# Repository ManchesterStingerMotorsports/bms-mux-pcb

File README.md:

# BMS MUX PCB

Initially the pcb scope was only for multiplexing 16 temperature sensor signals to 8, but the scope grew bigger and other stuffs were added.

Designed in Kicad V8

## V1 3D Render

### [Schematic](<docs/Schematic V1.pdf>)

### [Layout](<docs/PCB Layout V1.pdf>)

### [Copper Layers](<docs/PCB Copper Layers V1.pdf>)

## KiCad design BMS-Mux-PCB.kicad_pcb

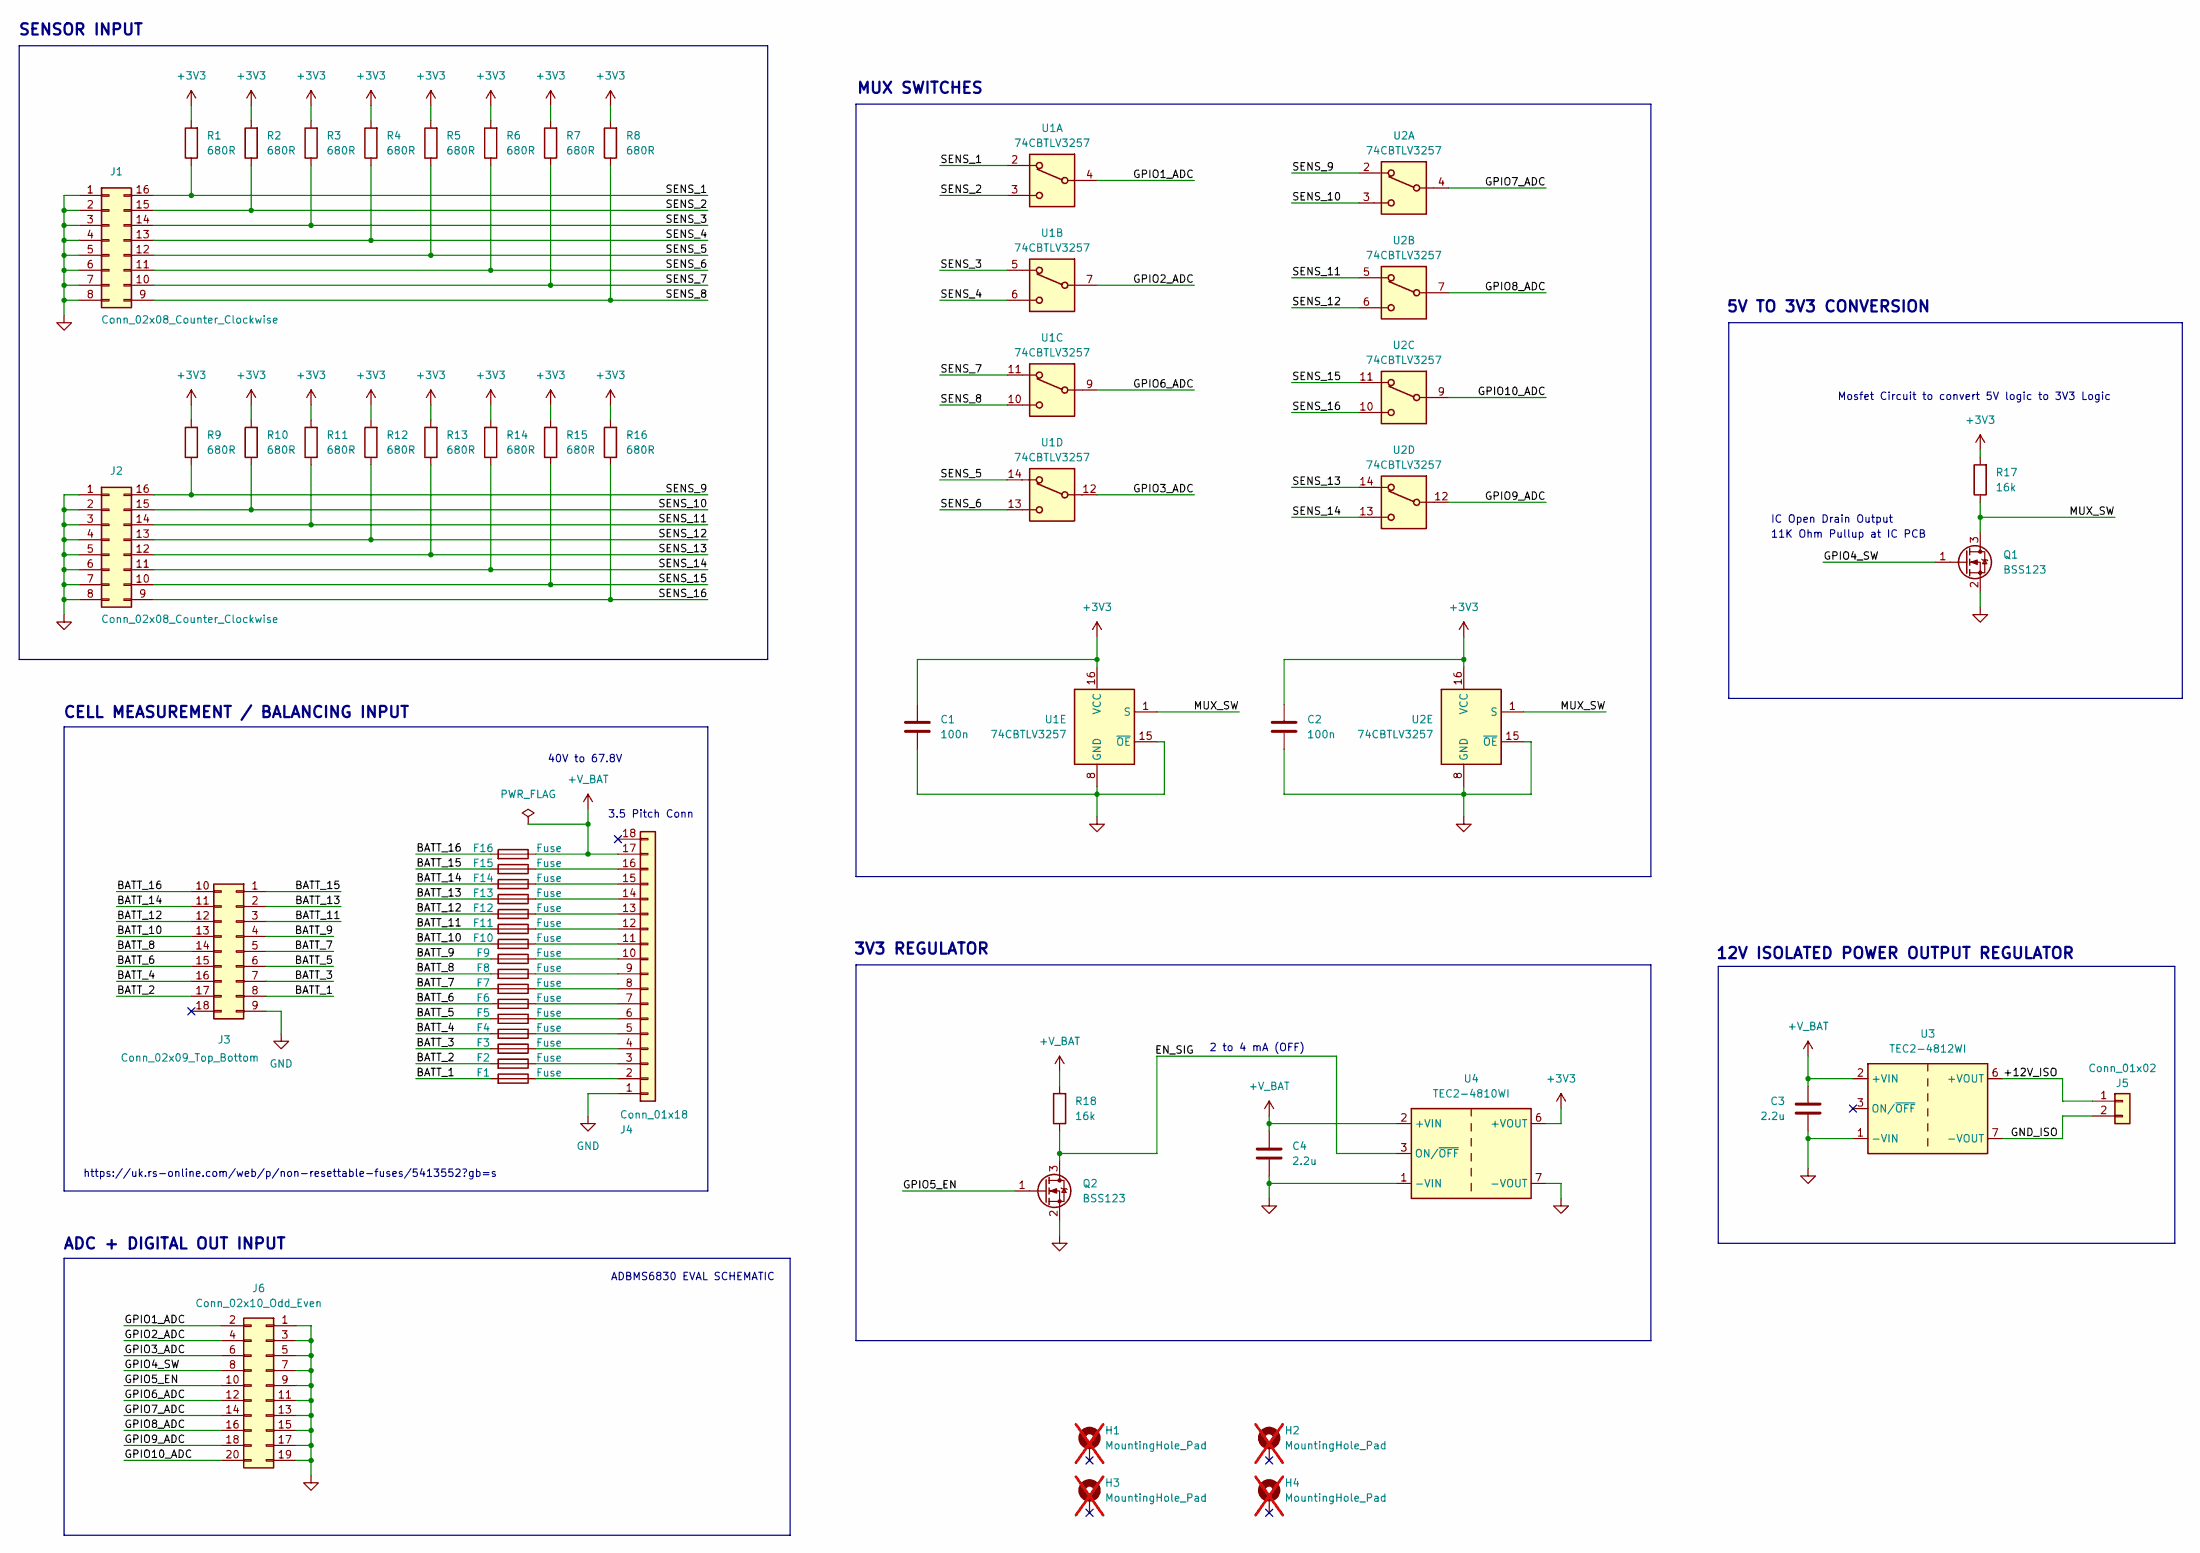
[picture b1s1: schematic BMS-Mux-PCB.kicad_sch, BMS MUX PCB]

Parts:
C1, C2: 100n; C_0603_1608Metric_Pad1.08x0.95mm_HandSolder; Manufacturer Part Number CL10B104KB85PND
C3, C4: 2.2u; C_1206_3216Metric_Pad1.33x1.80mm_HandSolder; Manufacturer Part Number 885382208016
F1, F2, F3, F4, F5, F6, F7, F8, F9, F10, F11, F12, F13, F14, F15, F16: Fuse; Fuse_1206_3216Metric_Pad1.42x1.75mm_HandSolder; Manufacturer Part Number 0466.250NR
H1, H2, H3, H4: MountingHole_Pad; Mounting_Hole; not fitted
J1, J2: Conn_02x08_Counter_Clockwise; Molex_Micro-Fit_3.0_43045-1600_2x08_P3.00mm_Horizontal; Manufacturer Part Number 43045-1600
J3: Conn_02x09_Top_Bottom; Molex_Micro-Fit_3.0_43045-1800_2x09_P3.00mm_Horizontal; Manufacturer Part Number 43045-1800
J4: Conn_01x18; Wago_734-148_1x18_P3.50mm_Vertical; Manufacturer Part Number 1945151 (x2)
J5: Conn_01x02; Molex_Micro-Fit_3.0_43650-0200_1x02_P3.00mm_Horizontal; Manufacturer Part Number 43650-0200
J6: Conn_02x10_Odd_Even; PinHeader_2x10_P2.54mm_Vertical; Manufacturer Part Number PH2-20-UA
Q1, Q2: BSS123; SOT-23; Manufacturer Part Number BSS123L
R1, R2, R3, R4, R5, R6, R7, R8, R9, R10, R11, R12, R13, R14, R15, R16: 680R; R_0805_2012Metric; Manufacturer Part Number ERA-6AEB681V
R17, R18: 16k; R_0805_2012Metric; Manufacturer Part Number ERA-6AEB163V
U1, U2: 74CBTLV3257; SOIC-16_3.9x9.9mm_P1.27mm; Manufacturer Part Number SN74LV4053ADR
U3: TEC2-4812WI; Converter_DCDC_TRACO_TMR-xxxx_THT; Manufacturer Part Number TEC2-4812WI
U4: TEC2-4810WI; Converter_DCDC_TRACO_TMR-xxxx_THT; Manufacturer Part Number TEC2-4810WI

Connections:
+3V3: C1.1, C2.1, R1.2, R2.2, R3.2, R4.2, R5.2, R6.2, R7.2, R8.2, R9.2, R10.2, R11.2, R12.2, R13.2, R14.2, R15.2, R16.2, R17.2, U1.16 (VCC), U2.16 (VCC), U4.6 (+VOUT)
+V_BAT: C3.1, C4.1, F16.1, J4.17, R18.2, U3.2 (+VIN), U4.2 (+VIN)
/+12V_ISO: J5.1, U3.6 (+VOUT)
/BATT_1: F1.2, J3.8
/BATT_2: F2.2, J3.17
/BATT_3: F3.2, J3.7
/BATT_4: F4.2, J3.16
/BATT_5: F5.2, J3.6
/BATT_6: F6.2, J3.15
/BATT_7: F7.2, J3.5
/BATT_8: F8.2, J3.14
/BATT_9: F9.2, J3.4
/BATT_10: F10.2, J3.13
/BATT_11: F11.2, J3.3
/BATT_12: F12.2, J3.12
/BATT_13: F13.2, J3.2
/BATT_14: F14.2, J3.11
/BATT_15: F15.2, J3.1
/BATT_16: F16.2, J3.10
/EN_SIG: Q2.3 (D), R18.1, U4.3 (ON/~OFF)
/GND_ISO: J5.2, U3.7 (-VOUT)
/GPIO1_ADC: J6.2, U1.4
/GPIO2_ADC: J6.4, U1.7
/GPIO3_ADC: J6.6, U1.12
/GPIO4_SW: J6.8, Q1.1 (G)
/GPIO5_EN: J6.10, Q2.1 (G)
/GPIO6_ADC: J6.12, U1.9
/GPIO7_ADC: J6.14, U2.4
/GPIO8_ADC: J6.16, U2.7
/GPIO9_ADC: J6.18, U2.12
/GPIO10_ADC: J6.20, U2.9
/MUX_SW: Q1.3 (D), R17.1, U1.1 (S), U2.1 (S)
/SENS_1: J1.16, R1.1, U1.2
/SENS_2: J1.15, R2.1, U1.3
/SENS_3: J1.14, R3.1, U1.5
/SENS_4: J1.13, R4.1, U1.6
/SENS_5: J1.12, R5.1, U1.14
/SENS_6: J1.11, R6.1, U1.13
/SENS_7: J1.10, R7.1, U1.11
/SENS_8: J1.9, R8.1, U1.10
/SENS_9: J2.16, R9.1, U2.2
/SENS_10: J2.15, R10.1, U2.3
/SENS_11: J2.14, R11.1, U2.5
/SENS_12: J2.13, R12.1, U2.6
/SENS_13: J2.12, R13.1, U2.14
/SENS_14: J2.11, R14.1, U2.13
/SENS_15: J2.10, R15.1, U2.11
/SENS_16: J2.9, R16.1, U2.10
GND: C1.2, C2.2, C3.2, C4.2, J1.1, J1.2, J1.3, J1.4, J1.5, J1.6, J1.7, J1.8, J2.1, J2.2, J2.3, J2.4, J2.5, J2.6, J2.7, J2.8, J3.9, J4.1, J6.1, J6.3, J6.5, J6.7, J6.9, J6.11, J6.13, J6.15, J6.17, J6.19, Q1.2 (S), Q2.2 (S), U1.8 (GND), U1.15 (~OE), U2.8 (GND), U2.15 (~OE), U3.1 (-VIN), U4.1 (-VIN), U4.7 (-VOUT)
unnamed: F1.1, J4.2
unnamed: F2.1, J4.3
unnamed: F3.1, J4.4
unnamed: F4.1, J4.5
unnamed: F5.1, J4.6
unnamed: F6.1, J4.7
unnamed: F7.1, J4.8
unnamed: F8.1, J4.9
unnamed: F9.1, J4.10
unnamed: F10.1, J4.11
unnamed: F11.1, J4.12
unnamed: F12.1, J4.13
unnamed: F13.1, J4.14
unnamed: F14.1, J4.15
unnamed: F15.1, J4.16

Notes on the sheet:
11K Ohm Pullup at IC PCB
SENSOR INPUT
ADBMS6830 EVAL SCHEMATIC
3V3 REGULATOR
40V to 67.8V
12V ISOLATED POWER OUTPUT REGULATOR
3.5 Pitch Conn
IC Open Drain Output
ADC + DIGITAL OUT INPUT
2 to 4 mA (OFF)
Mosfet Circuit to convert 5V logic to 3V3 Logic
MUX SWITCHES
https://uk.rs-online.com/web/p/non-resettable-fuses/5413552?gb=s
CELL MEASUREMENT / BALANCING INPUT
5V TO 3V3 CONVERSION

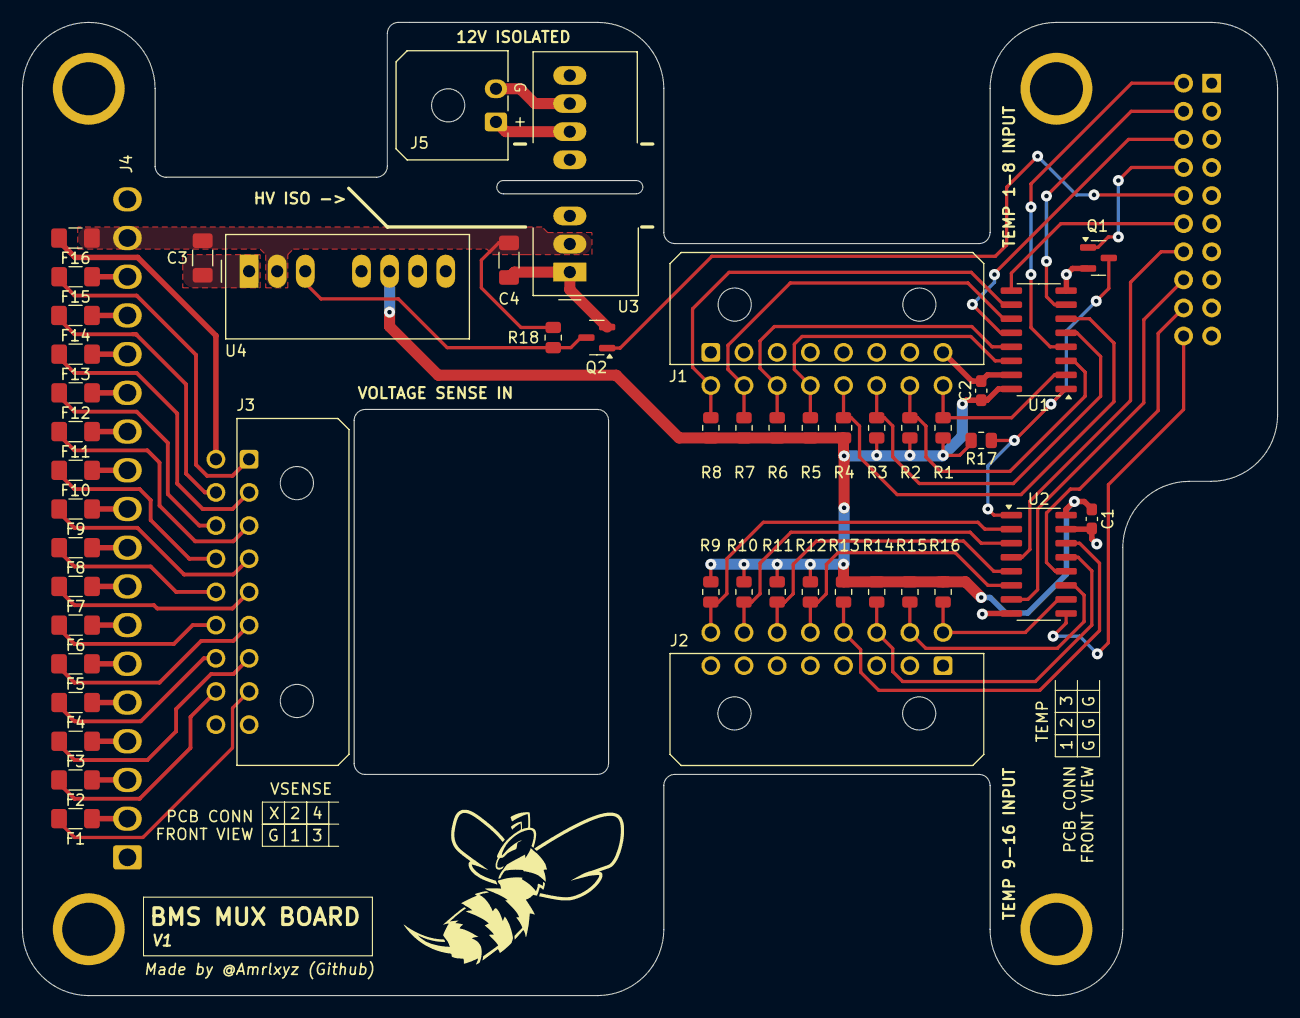
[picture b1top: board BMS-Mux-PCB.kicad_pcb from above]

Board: 2 copper layers, 113.5 x 88.0 mm, 54 parts (1 on the bottom side), 64 nets.

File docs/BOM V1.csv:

"Reference","Value","Datasheet","Footprint","Qty","DNP","Manufacturer Part Number"
"C1,C2","100n","~","Capacitor_SMD:C_0603_1608Metric_Pad1.08x0.95mm_HandSolder","2","","CL10B104KB85PND"
"C3,C4","2.2u","~","Capacitor_SMD:C_1206_3216Metric_Pad1.33x1.80mm_HandSolder","2","","885382208016"
"F1,F2,F3,F4,F5,F6,F7,F8,F9,F10,F11,F12,F13,F14,F15,F16","Fuse","~","Fuse:Fuse_1206_3216Metric_Pad1.42x1.75mm_HandSolder","16","","0466.250NR "
"J1,J2","Conn_02x08_Counter_Clockwise","~","BMS-Mux-footprints:Molex_Micro-Fit_3.0_43045-1600_2x08_P3.00mm_Horizontal","2","","43045-1600 "
"J3","Conn_02x09_Top_Bottom","~","BMS-Mux-footprints:Molex_Micro-Fit_3.0_43045-1800_2x09_P3.00mm_Horizontal","1","","43045-1800 "
"J4","Conn_01x18","~","Connector_Wago:Wago_734-148_1x18_P3.50mm_Vertical","1","","1945151 (x2)"
"J5","Conn_01x02","~","BMS-Mux-footprints:Molex_Micro-Fit_3.0_43650-0200_1x02_P3.00mm_Horizontal","1","","43650-0200"
"J6","Conn_02x10_Odd_Even","~","Connector_PinHeader_2.54mm:PinHeader_2x10_P2.54mm_Vertical","1","","PH2-20-UA"
"Q1,Q2","BSS123","http://www.diodes.com/assets/Datasheets/ds30366.pdf","Package_TO_SOT_SMD:SOT-23","2","","BSS123L"
"R1,R2,R3,R4,R5,R6,R7,R8,R9,R10,R11,R12,R13,R14,R15,R16","680R","~","Resistor_SMD:R_0805_2012Metric","16","","ERA-6AEB681V"
"R17,R18","16k","~","Resistor_SMD:R_0805_2012Metric","2","","ERA-6AEB163V"
"U1,U2","74CBTLV3257","http://www.ti.com/lit/ds/symlink/sn74cbtlv3257.pdf","Package_SO:SOIC-16_3.9x9.9mm_P1.27mm","2","","SN74LV4053ADR"
"U3","TEC2-4812WI","https://www.tracopower.com/products/tec2wi.pdf","Converter_DCDC:Converter_DCDC_TRACO_TMR-xxxx_THT","1","","TEC2-4812WI"
"U4","TEC2-4810WI","https://www.tracopower.com/products/tec2wi.pdf","Converter_DCDC:Converter_DCDC_TRACO_TMR-xxxx_THT","1","","TEC2-4810WI"

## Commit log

2025-02-09 first commit - before removing mosfet circuit
2025-02-09 Finished Schematic -> fuse and connector footprint needs changing
2025-02-12 progress
2025-02-13 updated footprints and started layout
2025-02-14 added softreset command after reset
2025-03-03 changed connector orientation and halfway routed
2025-03-04 V1 almost done - touching up silkscreen
2025-03-04 added pdfs and finalised V1
2025-03-07 added some small changes for manufacturing purposes and gerber file generated
2025-05-01 fixed the gpio pin name number (minor fix)
2025-05-26 added gitignore
2025-05-26 removed backups
